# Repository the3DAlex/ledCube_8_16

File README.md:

# ledCube_8_16
When cube will be ready install https://github.com/LuisMiCa/IRsmallDecoder in Arduino IDE.
From Example>IRsmallDecoder open HelloNEC example.
In the "IRsmallDecoder irDecoder(2);"  put your port number (in our case 10)
In "Serial.begin(250000);" put your terminal speed (Arduino Serial Monitor default value is 9600)
Burn sketch to cube.
Get your IR Pult and press all button one by one and remember it cmd.
Open LEDCube8_16.ino  and in loop void ander switch statement put thous cmd numbers. 
For example : "case 0x13:" where 0x13 - is yor cmd = button.
Note that not all pult works with this library. If no cmd shown - try another pult.

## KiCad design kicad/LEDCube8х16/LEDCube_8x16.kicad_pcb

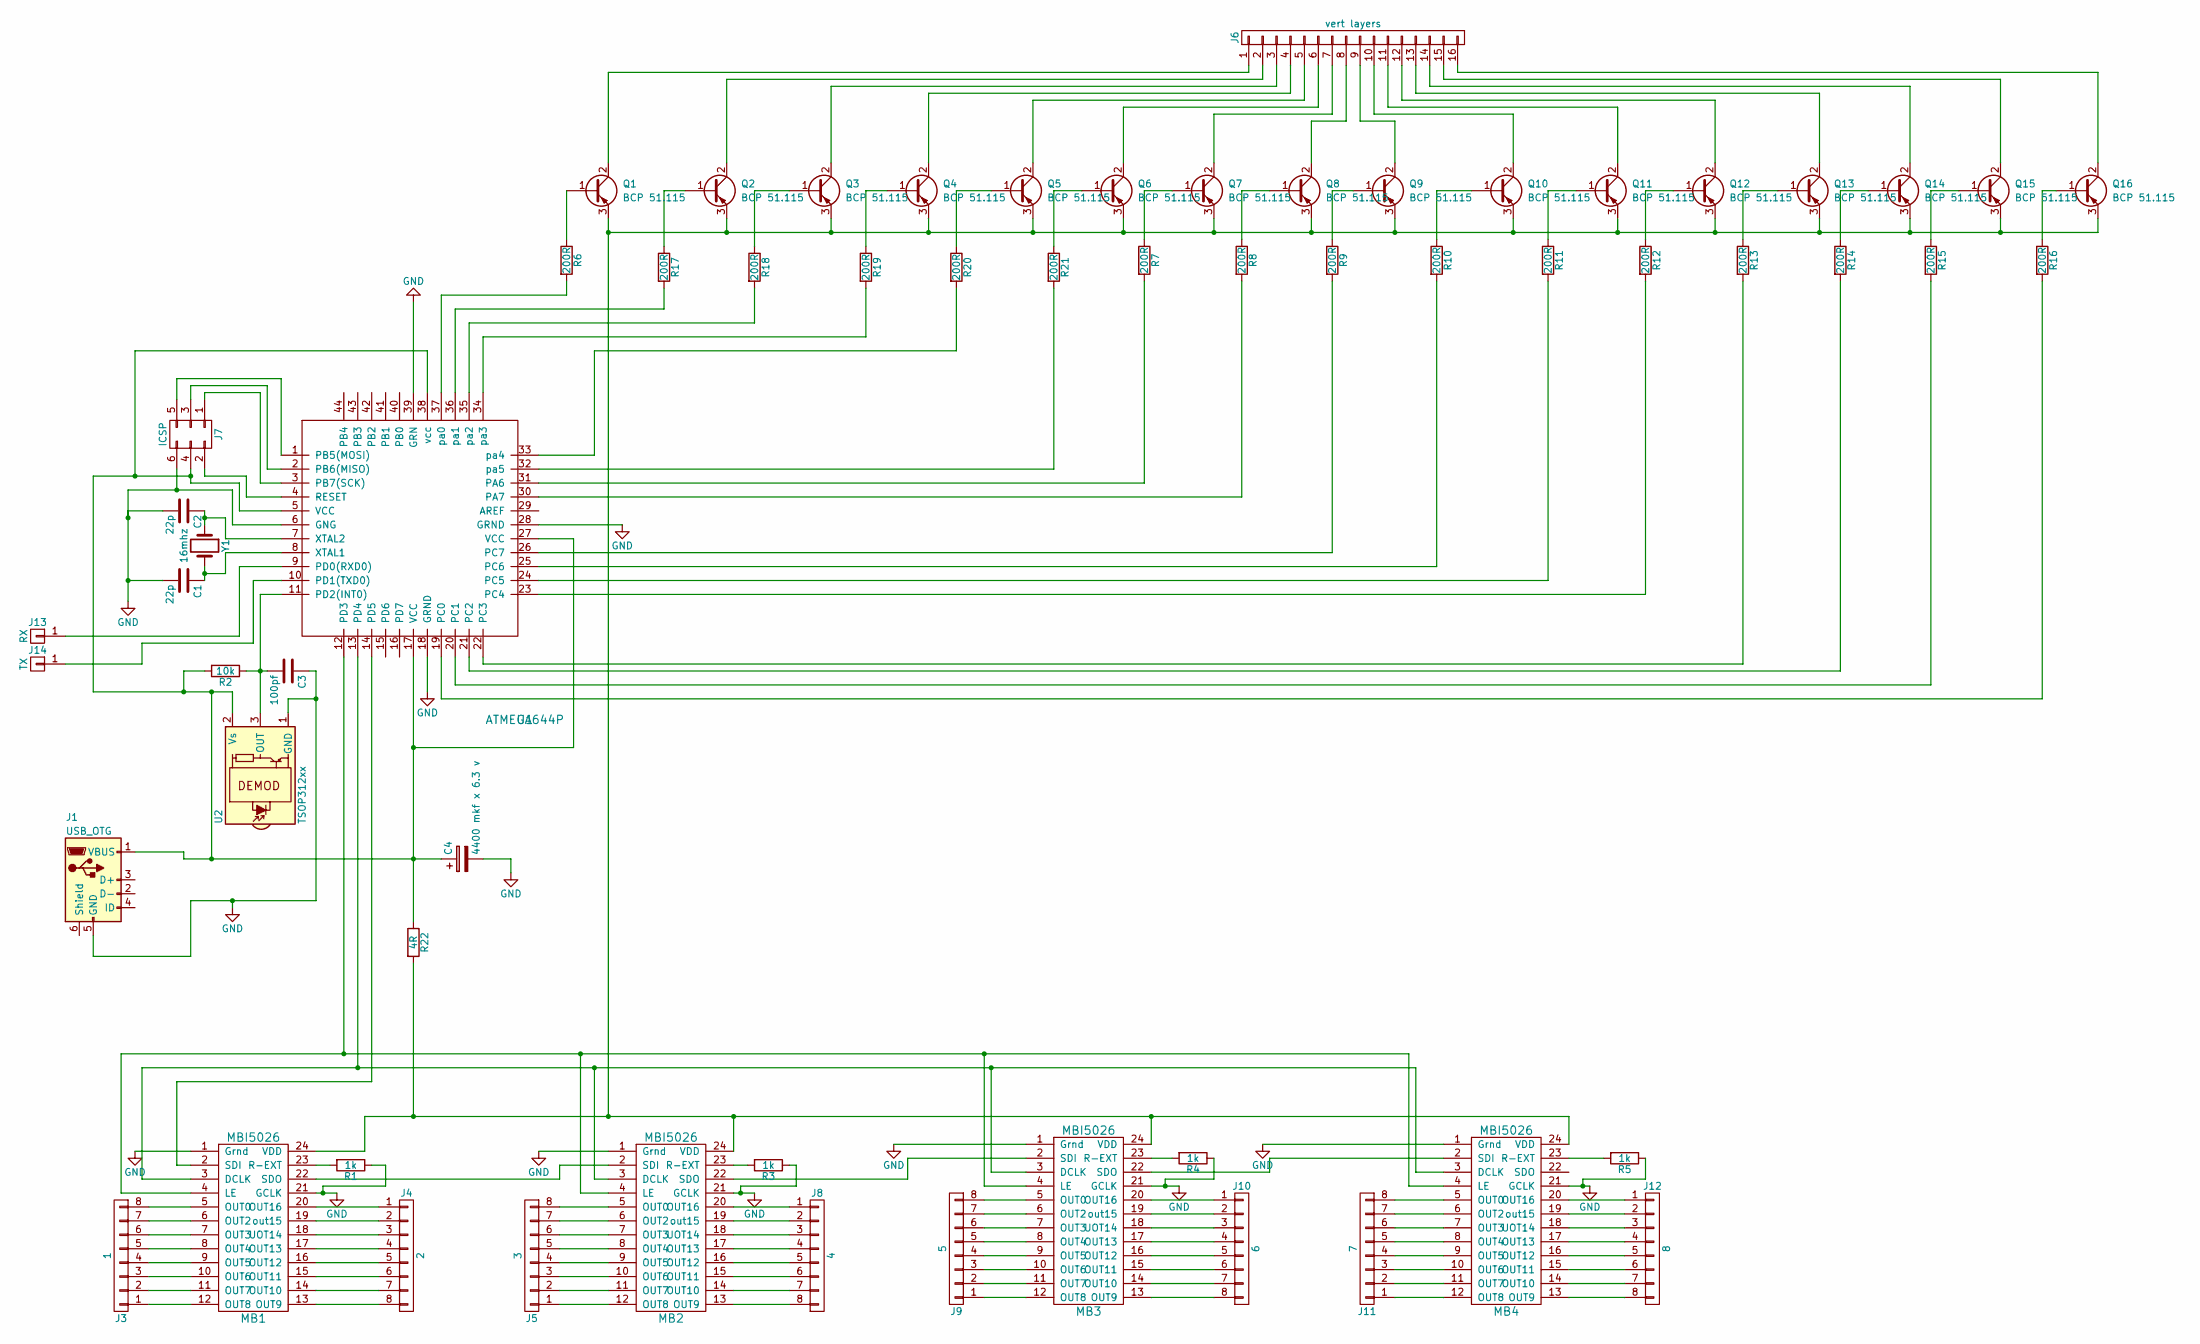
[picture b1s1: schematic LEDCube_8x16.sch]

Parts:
C1, C2: 22p; C_0805
C3: 100pf; C_0805
C4: 4400 mkf x 6.3 v; CP_Radial_D18.0mm_P7.50mm
J1: USB_OTG; USB_Micro-B
J3: 1; Pin_Header_Straight_1x08_Pitch1.00mm
J4: 2; Pin_Header_Straight_1x08_Pitch1.00mm
J5: 3; Pin_Header_Straight_1x08_Pitch1.00mm
J6: vert layers; Pin_Header_Straight_1x16_Pitch1.00mm
J7: ICSP; Pin_Header_Straight_2x03_Pitch2.54mm
J8: 4; Pin_Header_Straight_1x08_Pitch1.00mm
J9: 5; Pin_Header_Straight_1x08_Pitch1.00mm
J10: 6; Pin_Header_Straight_1x08_Pitch1.00mm
J11: 7; Pin_Header_Straight_1x08_Pitch1.00mm
J12: 8; Pin_Header_Straight_1x08_Pitch1.00mm
J13: RX; Pin_Header_Straight_1x01_Pitch2.54mm
J14: TX; Pin_Header_Straight_1x01_Pitch2.54mm
MB1, MB2, MB3, MB4: MBI5026; MBI5030
Q1, Q2, Q3, Q4, Q5, Q6, Q7, Q8, Q9, Q10, Q11, Q12, Q13, Q14, Q15, Q16: BCP 51.115; TO-92_Molded_Wide
R1, R3, R4, R5: 1k; R_0805
R2: 10k; R_0805
R6, R7, R8, R9, R10, R11, R12, R13, R14, R15, R16, R17, R18, R19, R20, R21: 200R; R_0805
R22: 4R; R_Axial_DIN0411_L9.9mm_D3.6mm_P7.62mm_Vertical
U1: ATMEGA644P; TQFP-44_10x10mm_Pitch0.8mm
U2: TSOP312xx; IRReceiver_Vishay_CAST-3pin
Y1: 16mhz; Crystal_HC49-U_Vertical

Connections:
GND: C1.2, C2.2, C3.1, C4.2, J1.5 (GND), J7.6, MB1.1 (Grnd), MB1.21 (GCLK), MB2.1 (Grnd), MB2.21 (GCLK), MB3.1 (Grnd), MB3.21 (GCLK), MB4.1 (Grnd), MB4.21 (GCLK), R1.1, R3.1, R4.1, R5.1, U1.6 (GNG), U1.18 (GRND), U1.28 (GRND), U1.39 (GRN), U2.1 (GND)
unnamed: C1.1, U1.8 (XTAL1), Y1.2
unnamed: C2.1, U1.7 (XTAL2), Y1.1
unnamed: C3.2, R2.1, U1.11 (PD2(INT0)), U2.3 (OUT)
unnamed: C4.1, J1.1 (VBUS), J7.4, R2.2, R22.1, U1.5 (VCC), U1.17 (VCC), U1.27 (VCC), U1.38 (vcc), U2.2 (Vs)
unnamed: J3.1, MB1.12 (OUT8)
unnamed: J3.2, MB1.11 (OUT7)
unnamed: J3.3, MB1.10 (OUT6)
unnamed: J3.4, MB1.9 (OUT5)
unnamed: J3.5, MB1.8 (OUT4)
unnamed: J3.6, MB1.7 (OUT3)
unnamed: J3.7, MB1.6 (OUT2)
unnamed: J3.8, MB1.5 (OUT0)
unnamed: J4.1, MB1.20 (OUT16)
unnamed: J4.2, MB1.19 (out15)
unnamed: J4.3, MB1.18 (UOT14)
unnamed: J4.4, MB1.17 (OUT13)
unnamed: J4.5, MB1.16 (OUT12)
unnamed: J4.6, MB1.15 (OUT11)
unnamed: J4.7, MB1.14 (OUT10)
unnamed: J4.8, MB1.13 (OUT9)
unnamed: J5.1, MB2.12 (OUT8)
unnamed: J5.2, MB2.11 (OUT7)
unnamed: J5.3, MB2.10 (OUT6)
unnamed: J5.4, MB2.9 (OUT5)
unnamed: J5.5, MB2.8 (OUT4)
unnamed: J5.6, MB2.7 (OUT3)
unnamed: J5.7, MB2.6 (OUT2)
unnamed: J5.8, MB2.5 (OUT0)
unnamed: J6.1, Q1.2 (C)
unnamed: J6.2, Q2.2 (C)
unnamed: J6.3, Q3.2 (C)
unnamed: J6.4, Q4.2 (C)
unnamed: J6.5, Q5.2 (C)
unnamed: J6.6, Q6.2 (C)
unnamed: J6.7, Q7.2 (C)
unnamed: J6.8, Q8.2 (C)
unnamed: J6.9, Q9.2 (C)
unnamed: J6.10, Q10.2 (C)
unnamed: J6.11, Q11.2 (C)
unnamed: J6.12, Q12.2 (C)
unnamed: J6.13, Q13.2 (C)
unnamed: J6.14, Q14.2 (C)
unnamed: J6.15, Q15.2 (C)
unnamed: J6.16, Q16.2 (C)
unnamed: J7.1, U1.3 (PB7(SCK))
unnamed: J7.2, U1.4 (RESET)
unnamed: J7.3, U1.2 (PB6(MISO))
unnamed: J7.5, U1.1 (PB5(MOSI))
unnamed: J8.1, MB2.20 (OUT16)
unnamed: J8.2, MB2.19 (out15)
unnamed: J8.3, MB2.18 (UOT14)
unnamed: J8.4, MB2.17 (OUT13)
unnamed: J8.5, MB2.16 (OUT12)
unnamed: J8.6, MB2.15 (OUT11)
unnamed: J8.7, MB2.14 (OUT10)
unnamed: J8.8, MB2.13 (OUT9)
unnamed: J9.1, MB3.12 (OUT8)
unnamed: J9.2, MB3.11 (OUT7)
unnamed: J9.3, MB3.10 (OUT6)
unnamed: J9.4, MB3.9 (OUT5)
unnamed: J9.5, MB3.8 (OUT4)
unnamed: J9.6, MB3.7 (OUT3)
unnamed: J9.7, MB3.6 (OUT2)
unnamed: J9.8, MB3.5 (OUT0)
unnamed: J10.1, MB3.20 (OUT16)
unnamed: J10.2, MB3.19 (out15)
unnamed: J10.3, MB3.18 (UOT14)
unnamed: J10.4, MB3.17 (OUT13)
unnamed: J10.5, MB3.16 (OUT12)
unnamed: J10.6, MB3.15 (OUT11)
unnamed: J10.7, MB3.14 (OUT10)
unnamed: J10.8, MB3.13 (OUT9)
unnamed: J11.1, MB4.12 (OUT8)
unnamed: J11.2, MB4.11 (OUT7)
unnamed: J11.3, MB4.10 (OUT6)
unnamed: J11.4, MB4.9 (OUT5)
unnamed: J11.5, MB4.8 (OUT4)
unnamed: J11.6, MB4.7 (OUT3)
unnamed: J11.7, MB4.6 (OUT2)
unnamed: J11.8, MB4.5 (OUT0)
unnamed: J12.1, MB4.20 (OUT16)
unnamed: J12.2, MB4.19 (out15)
unnamed: J12.3, MB4.18 (UOT14)
unnamed: J12.4, MB4.17 (OUT13)
unnamed: J12.5, MB4.16 (OUT12)
unnamed: J12.6, MB4.15 (OUT11)
unnamed: J12.7, MB4.14 (OUT10)
unnamed: J12.8, MB4.13 (OUT9)
unnamed: J13.1, U1.9 (PD0(RXD0))
unnamed: J14.1, U1.10 (PD1(TXD0))
unnamed: MB1.2 (SDI), U1.14 (PD5)
unnamed: MB1.3 (DCLK), MB2.3 (DCLK), MB3.3 (DCLK), MB4.3 (DCLK), U1.13 (PD4)
unnamed: MB1.4 (LE), MB2.4 (LE), MB3.4 (LE), MB4.4 (LE), U1.12 (PD3)
unnamed: MB1.22 (SDO), MB2.2 (SDI)
unnamed: MB1.23 (R-EXT), R1.2
unnamed: MB1.24 (VDD), MB2.24 (VDD), MB3.24 (VDD), MB4.24 (VDD), Q1.3 (E), Q2.3 (E), Q3.3 (E), Q4.3 (E), Q5.3 (E), Q6.3 (E), Q7.3 (E), Q8.3 (E), Q9.3 (E), Q10.3 (E), Q11.3 (E), Q12.3 (E), Q13.3 (E), Q14.3 (E), Q15.3 (E), Q16.3 (E), R22.2
unnamed: MB2.22 (SDO), MB3.2 (SDI)
unnamed: MB2.23 (R-EXT), R3.2
unnamed: MB3.22 (SDO), MB4.2 (SDI)
unnamed: MB3.23 (R-EXT), R4.2
unnamed: MB4.23 (R-EXT), R5.2
unnamed: Q1.1 (B), R6.1
unnamed: Q2.1 (B), R17.1
unnamed: Q3.1 (B), R18.1
unnamed: Q4.1 (B), R19.1
unnamed: Q5.1 (B), R20.1
unnamed: Q6.1 (B), R21.1
unnamed: Q7.1 (B), R7.1
unnamed: Q8.1 (B), R8.1
unnamed: Q9.1 (B), R9.1
unnamed: Q10.1 (B), R10.1
unnamed: Q11.1 (B), R11.1
unnamed: Q12.1 (B), R12.1
unnamed: Q13.1 (B), R13.1
unnamed: Q14.1 (B), R14.1
unnamed: Q15.1 (B), R15.1
unnamed: Q16.1 (B), R16.1
unnamed: R6.2, U1.37 (pa0)
unnamed: R7.2, U1.31 (PA6)
unnamed: R8.2, U1.30 (PA7)
unnamed: R9.2, U1.26 (PC7)
unnamed: R10.2, U1.25 (PC6)
unnamed: R11.2, U1.24 (PC5)
unnamed: R12.2, U1.23 (PC4)
unnamed: R13.2, U1.22 (PC3)
unnamed: R14.2, U1.21 (PC2)
unnamed: R15.2, U1.20 (PC1)
unnamed: R16.2, U1.19 (PC0)
unnamed: R17.2, U1.36 (pa1)
unnamed: R18.2, U1.35 (pa2)
unnamed: R19.2, U1.34 (pa3)
unnamed: R20.2, U1.33 (pa4)
unnamed: R21.2, U1.32 (pa5)

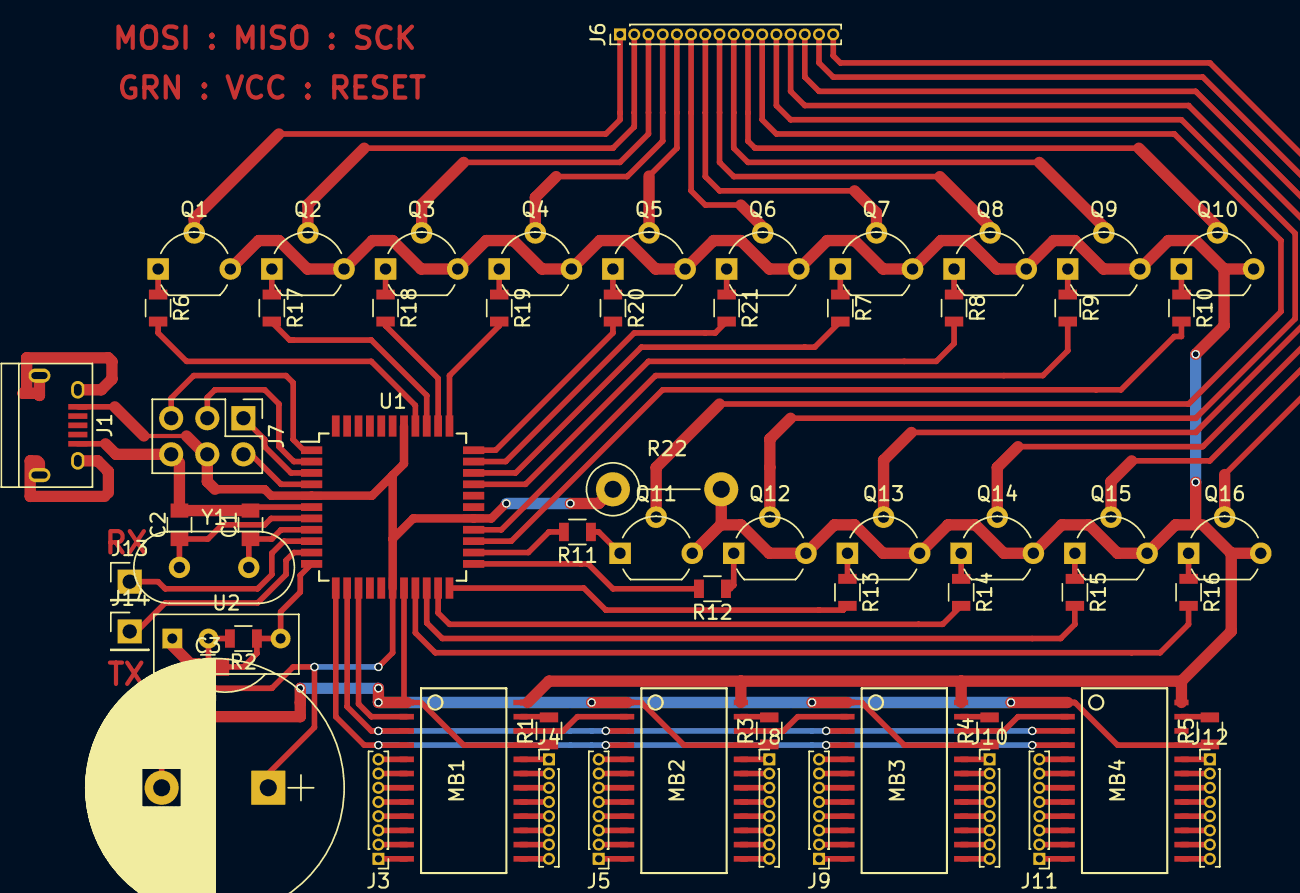
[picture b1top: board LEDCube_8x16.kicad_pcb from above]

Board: 2 copper layers, 62 parts (0 on the bottom side), 134 nets.

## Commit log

2021-12-02 kicad files
2021-12-07 prefinished scetch
2021-12-07 forgot to add the sketch )
2021-12-08 fixes in scheme
2021-12-08 code rewiev
2021-12-08 fixes
2021-12-08 added resistor between mcu and leds
2021-12-11 added 2 new modes (6 & 7 was turned off but procedures stay there. if you want - you may include they)
